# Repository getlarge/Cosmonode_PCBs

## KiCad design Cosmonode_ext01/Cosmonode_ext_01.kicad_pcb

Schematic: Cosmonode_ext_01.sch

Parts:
C1, C2, C3, C4: 100nF; C_0603_HandSoldering
J1: GS2
J3, J5: CONN_01X08; Socket_Strip_Straight_1x08_Pitch2.54mm
J4: Aloes_Logo; Aloes_mini
J6: OSHW_Logo; OSHW-Logo_5.7x6mm_SilkScreen
J8, J9: GS3
R1: 4.7k; R_0603_HandSoldering
U1: TSL2561T(6P-3.8X2.6MM); TMB6-1.55-3.8X2.6MM
U2: BMP180
U3: SI7020-A20-YM0R; SON100P300X300X80-7N

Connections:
+3V3: J5.2, J5.3, J9.1 (G1)
/A0: J3.6
/A1: J3.7
/A4: J5.6, U1.6 (SDA), U2.6 (SDA), U3.1 (SDA)
/A5: J5.7, U1.4 (SCL), U2.5 (SCL), U3.6 (SCL)
/A6: J3.8
/A7: J5.8
/BAT+: J5.1
/D3: J3.1, U1.5 (INT)
/D4: J3.2, J9.3 (G3)
/D5: J3.3
/D6: J3.4, J8.3 (G3)
/D7: J3.5
GND: J5.4, J5.5, J8.1 (G1)
unnamed: C1.1, C2.1, C3.1, C4.1, J1.1 (G1), J9.2 (G2), U1.1 (VDD), U2.2 (VDD), U2.3 (VDDIO), U3.5 (VDD)
unnamed: C1.2, C2.2, C3.2, C4.2, J8.2 (G2), R1.2, U1.3 (GND), U2.7 (GND), U3.2 (GND)
unnamed: J1.2 (G2), R1.1, U1.2 (ADDR)

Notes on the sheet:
D6 as GND
D4 as +3.3V

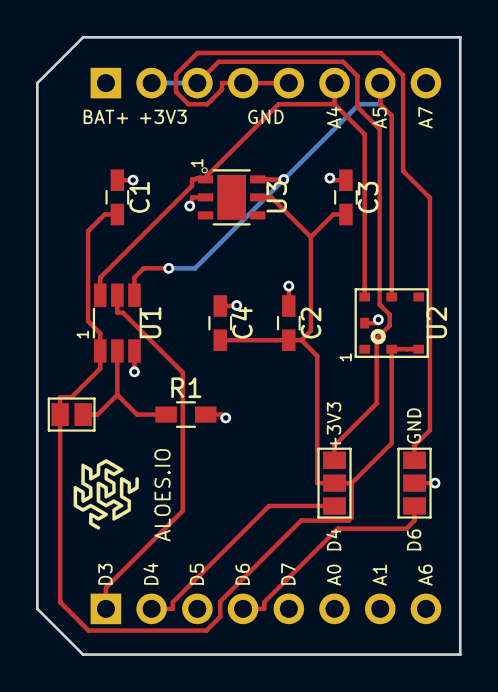
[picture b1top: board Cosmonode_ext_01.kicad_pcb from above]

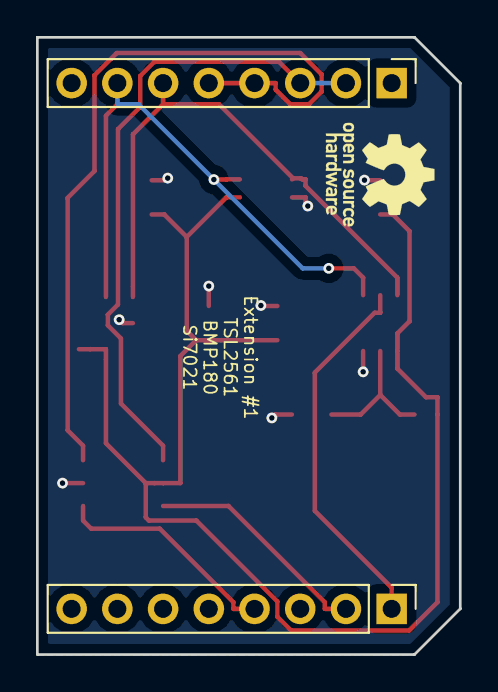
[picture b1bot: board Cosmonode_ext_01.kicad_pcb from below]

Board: 2 copper layers, 23.5 x 34.3 mm, 15 parts (3 on the bottom side), 10 nets.

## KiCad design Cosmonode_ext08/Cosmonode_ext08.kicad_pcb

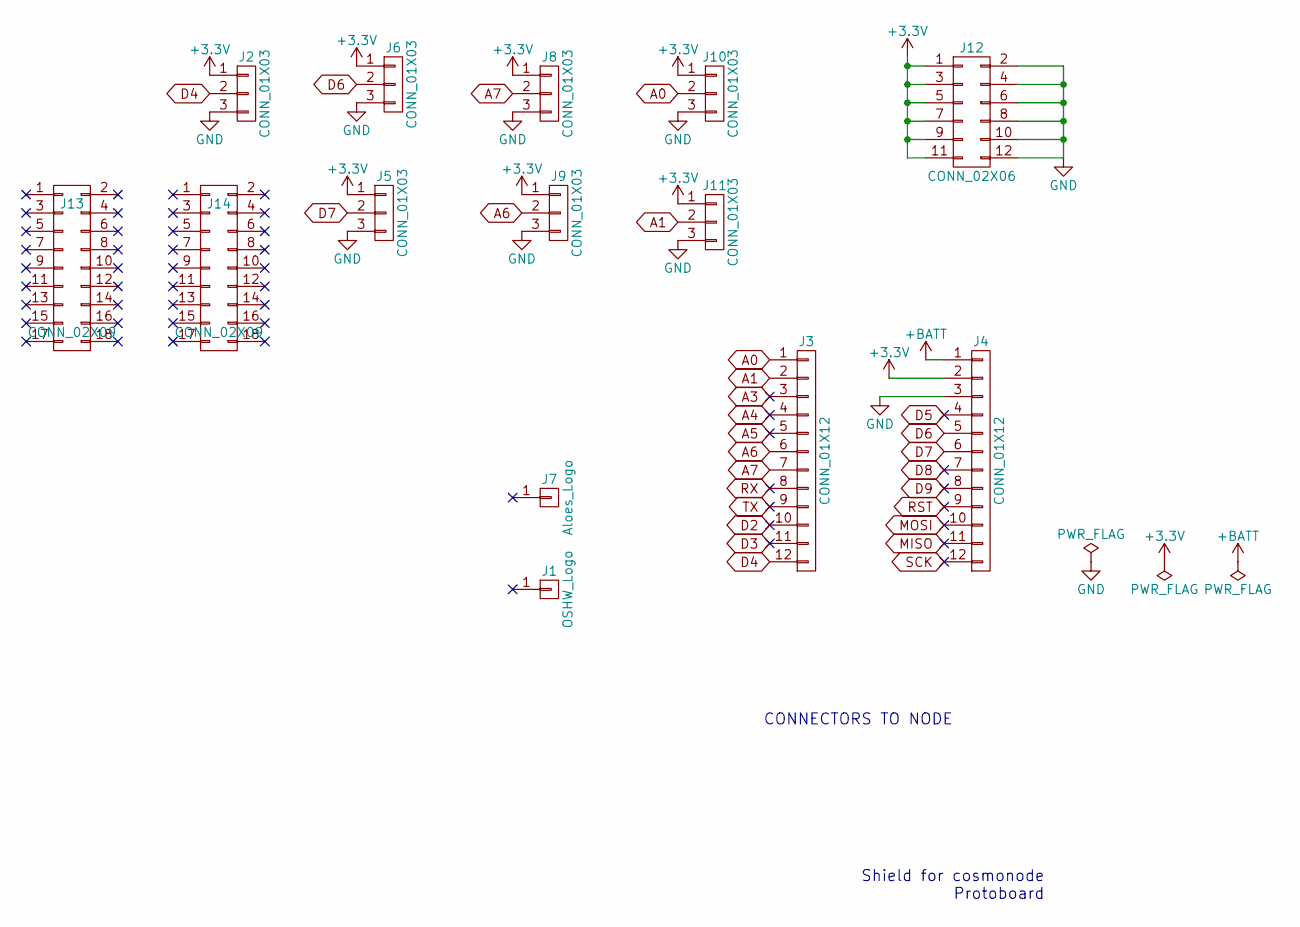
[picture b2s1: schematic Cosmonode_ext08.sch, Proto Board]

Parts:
J1: OSHW_Logo; OSHW-Logo_5.7x6mm_SilkScreen
J2, J5, J6, J8, J9, J10, J11: CONN_01X03; Pin_Header_Straight_1x03_Pitch2.54mm
J3, J4: CONN_01X12; Socket_Strip_Straight_1x12_Pitch2.54mm
J7: Aloes_Logo; Aloes_mini
J12: CONN_02X06; Pin_Header_Straight_2x06_Pitch2.54mm
J13, J14: CONN_02X09; Pin_Header_Straight_2x09_Pitch2.54mm

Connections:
+3V3: J2.1, J4.2, J5.1, J6.1, J8.1, J9.1, J10.1, J11.1, J12.1, J12.3, J12.5, J12.7, J12.9, J12.11
+BATT: J4.1
A0: J3.1, J10.2
A1: J3.2, J11.2
A3: J3.3
A4: J3.4
A5: J3.5
A6: J3.6, J9.2
A7: J3.7, J8.2
D2: J3.10
D3: J3.11
D4: J2.2, J3.12
D5: J4.4
D6: J4.5, J6.2
D7: J4.6, J5.2
D8: J4.7
D9: J4.8
GND: J2.3, J4.3, J5.3, J6.3, J8.3, J9.3, J10.3, J11.3, J12.2, J12.4, J12.6, J12.8, J12.10, J12.12
MISO: J4.11
MOSI: J4.10
RST: J4.9
RX: J3.8
SCK: J4.12
TX: J3.9

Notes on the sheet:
Shield for cosmonode Protoboard
CONNECTORS TO NODE

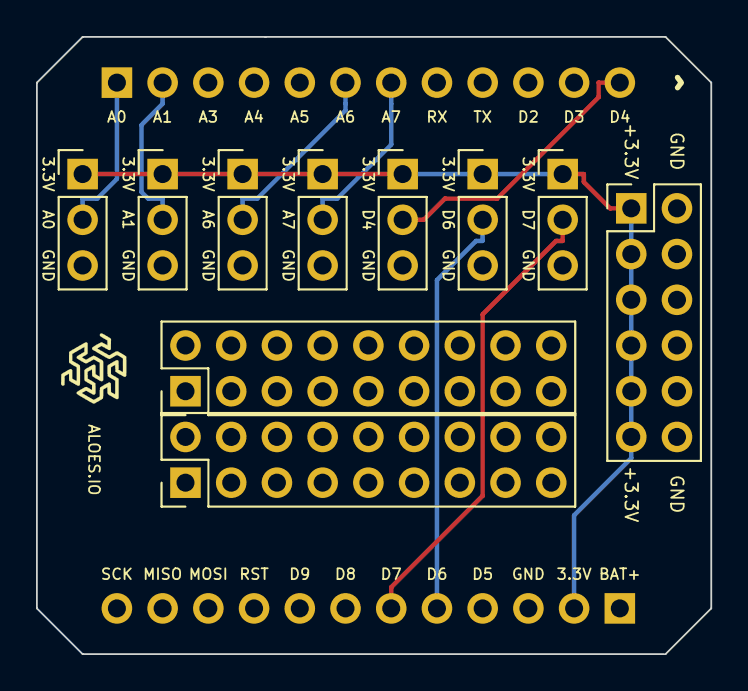
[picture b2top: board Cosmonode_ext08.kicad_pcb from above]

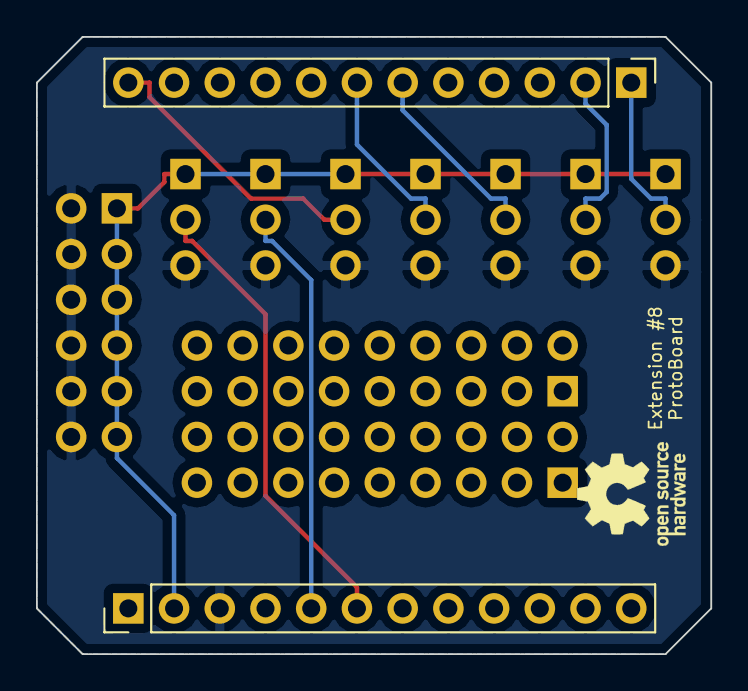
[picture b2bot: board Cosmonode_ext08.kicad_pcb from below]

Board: 2 copper layers, 37.5 x 34.3 mm, 14 parts (3 on the bottom side), 9 nets.

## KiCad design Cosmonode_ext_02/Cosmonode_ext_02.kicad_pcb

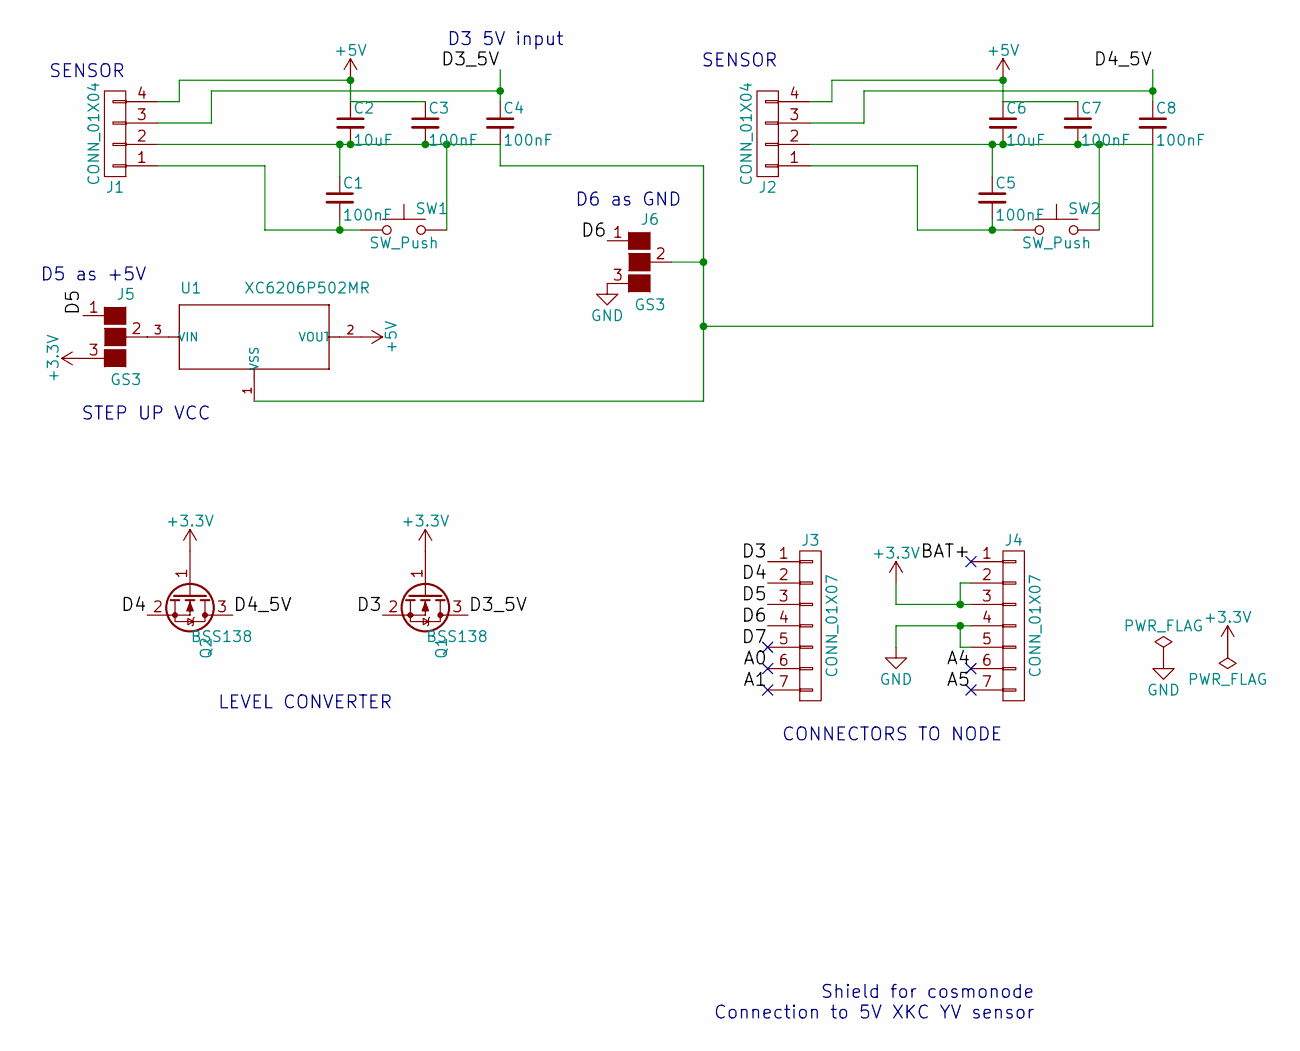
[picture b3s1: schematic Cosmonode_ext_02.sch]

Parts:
C1, C3, C4, C5, C7, C8: 100nF; C_0603_HandSoldering
C2, C6: 10uF; C_0603_HandSoldering
J1, J2: CONN_01X04; JST_XH_B04B-XH-A_04x2.50mm_Straight
J3, J4: CONN_01X07; Pin_Header_Straight_1x07_Pitch2.54mm
J5, J6: GS3
Q1, Q2: BSS138; SOT-23_Handsoldering
SW1, SW2: SW_Push; SW_SPST_B3U-1000P
U1: XC6206P502MR; SOT-23_Handsoldering

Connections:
+3V3: J4.2, J4.3, J5.3 (G3), Q1.1 (G), Q2.1 (G)
+5V: C2.1, C3.1, C6.1, C7.1, J1.4, J2.4, U1.2 (VOUT)
/A0: J3.6
/A1: J3.7
/A4: J4.6
/A5: J4.7
/BAT+: J4.1
/D3: J3.1, Q1.2 (S)
/D3_5V: C4.1, J1.3, Q1.3 (D)
/D4: J3.2, Q2.2 (S)
/D4_5V: C8.1, J2.3, Q2.3 (D)
/D5: J3.3, J5.1 (G1)
/D6: J3.4, J6.1 (G1)
/D7: J3.5
GND: J4.4, J4.5, J6.3 (G3)
unnamed: C1.1, C2.2, C3.2, C4.2, C5.1, C6.2, C7.2, C8.2, J1.2, J2.2, J6.2 (G2), SW1.2, SW2.2, U1.1 (VSS)
unnamed: C1.2, J1.1, SW1.1
unnamed: C5.2, J2.1, SW2.1
unnamed: J5.2 (G2), U1.3 (VIN)

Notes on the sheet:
D5 as +5V
D6 as GND
Shield for cosmonode Connection to 5V XKC YV sensor
D3 5V input
CONNECTORS TO NODE
LEVEL CONVERTER
STEP UP VCC
SENSOR

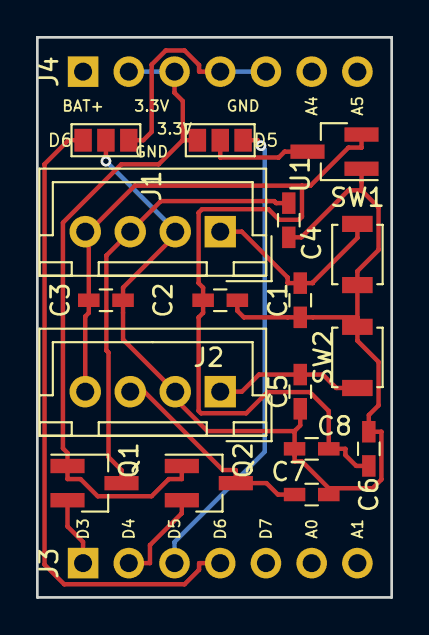
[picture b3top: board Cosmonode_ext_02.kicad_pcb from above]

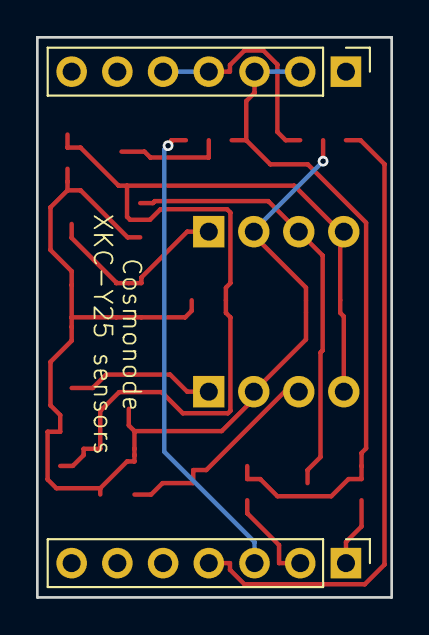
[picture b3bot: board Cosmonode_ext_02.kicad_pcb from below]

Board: 2 copper layers, 19.7 x 31.1 mm, 19 parts (2 on the bottom side), 13 nets.

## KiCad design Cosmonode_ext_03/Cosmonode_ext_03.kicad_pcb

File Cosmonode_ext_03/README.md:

# Cosmonode_ext_03

Extension 3 : includes 2 connectors for I2C 3.3V

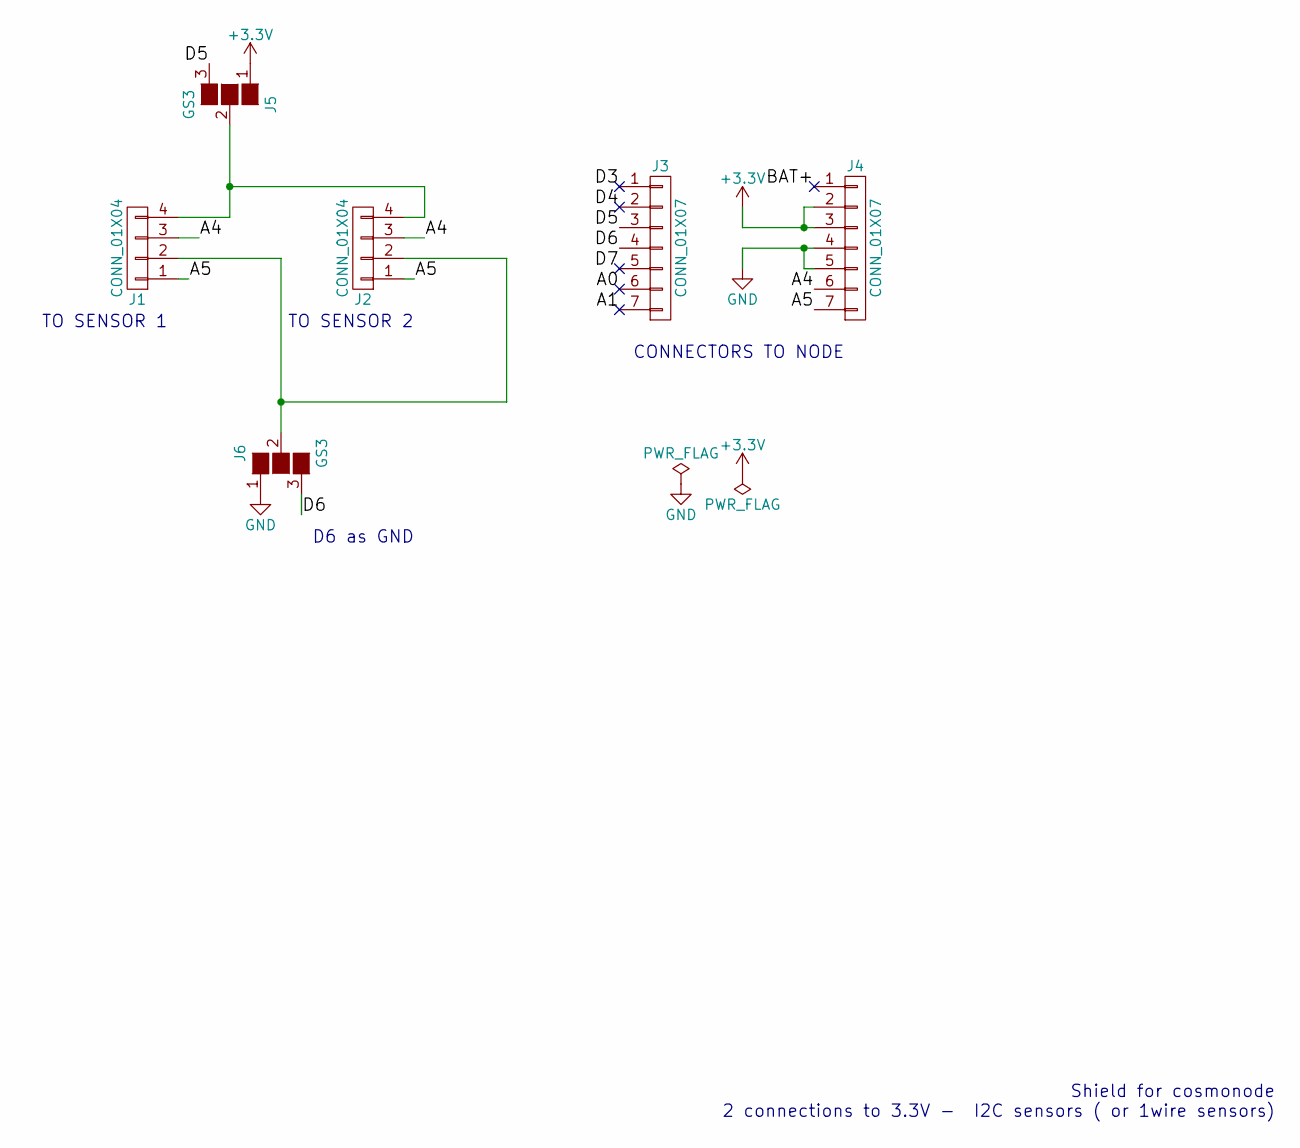
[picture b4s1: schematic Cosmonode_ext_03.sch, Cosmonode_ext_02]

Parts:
J1, J2: CONN_01X04; JST_XH_B04B-XH-A_04x2.50mm_Straight
J3, J4: CONN_01X07; Pin_Header_Straight_1x07_Pitch2.54mm
J5, J6: GS3

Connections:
+3V3: J4.2, J4.3, J5.1 (G1)
/A0: J3.6
/A1: J3.7
/A4: J1.3, J2.3, J4.6
/A5: J1.1, J2.1, J4.7
/BAT+: J4.1
/D3: J3.1
/D4: J3.2
/D5: J3.3, J5.3 (G3)
/D6: J3.4, J6.3 (G3)
/D7: J3.5
GND: J4.4, J4.5, J6.1 (G1)
unnamed: J1.2, J2.2, J6.2 (G2)
unnamed: J1.4, J2.4, J5.2 (G2)

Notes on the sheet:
D6 as GND
Shield for cosmonode 2 connections to 3.3V - I2C sensors ( or 1wire sensors)
CONNECTORS TO NODE
TO SENSOR 1
TO SENSOR 2

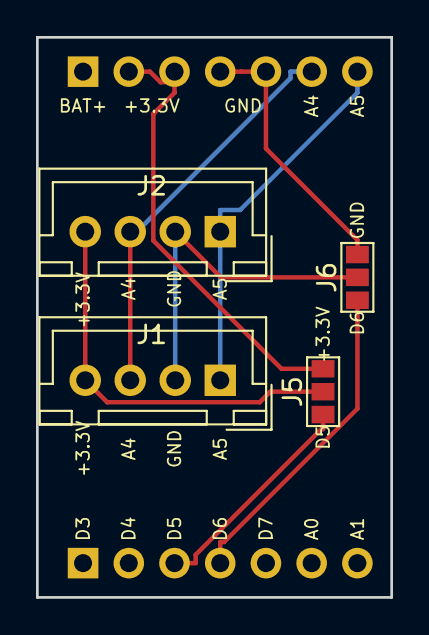
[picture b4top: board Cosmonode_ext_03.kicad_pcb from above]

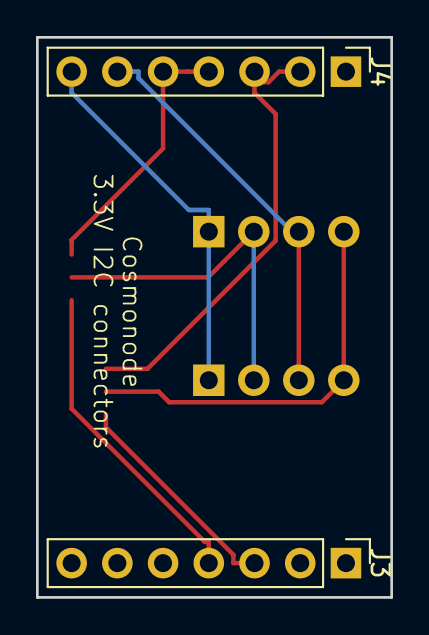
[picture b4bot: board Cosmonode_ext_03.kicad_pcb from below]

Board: 2 copper layers, 19.7 x 31.1 mm, 6 parts (2 on the bottom side), 8 nets.

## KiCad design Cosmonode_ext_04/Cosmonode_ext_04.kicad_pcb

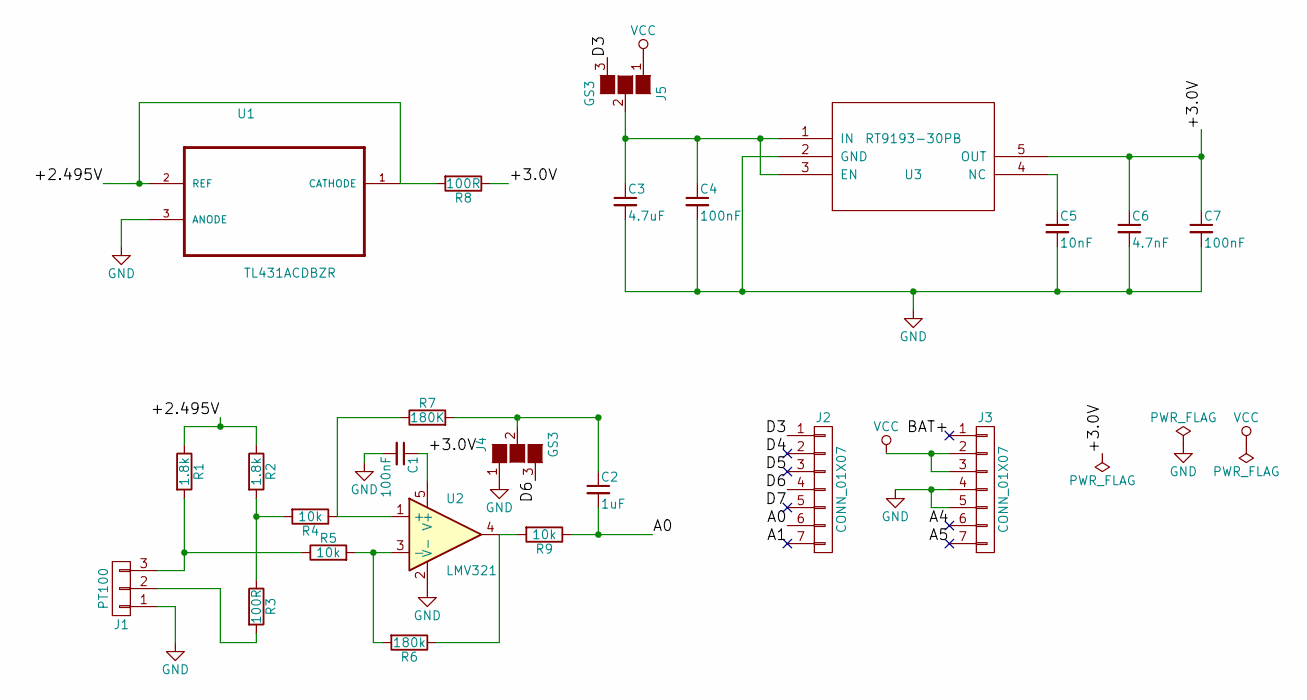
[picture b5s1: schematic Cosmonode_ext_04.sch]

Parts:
C1, C4, C7: 100nF; C_0603_HandSoldering
C2: 1uF; C_0603_HandSoldering
C3: 4.7uF; C_0603_HandSoldering
C5: 10nF; C_0603_HandSoldering
C6: 4.7nF; C_0603_HandSoldering
J1: PT100; JST_PH_B3B-PH-K_03x2.00mm_Straight
J2, J3: CONN_01X07; Pin_Header_Straight_1x07_Pitch2.54mm
J4, J5: GS3
R1, R2: 1.8k; R_0603_HandSoldering
R3, R8: 100R; R_0603_HandSoldering
R4, R5, R9: 10k; R_0603_HandSoldering
R6: 180k; R_0603_HandSoldering
R7: 180K; R_0603_HandSoldering
U1: TL431ACDBZR; SOT-23_Handsoldering
U2: LMV321; SOT-23-5_HandSoldering
U3: RT9193-30PB; SOT-23-5_HandSoldering

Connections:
/+2.495V: R1.1, R2.1, R8.2, U1.1 (CATHODE), U1.2 (REF)
/+3.0V: C1.1, C6.1, C7.1, R8.1, U2.5 (V+), U3.5 (OUT)
/A0: C2.2, J2.6, R9.1
/A1: J2.7
/A4: J3.6
/A5: J3.7
/BAT+: J3.1
/D3: J2.1, J5.3 (G3)
/D4: J2.2
/D5: J2.3
/D6: J2.4, J4.3 (G3)
/D7: J2.5
GND: C1.2, C3.2, C4.2, C5.2, C6.2, C7.2, J1.1, J3.4, J3.5, J4.1 (G1), U1.3 (ANODE), U2.2 (V-), U3.2 (GND)
unnamed: C2.1, J4.2 (G2), R7.2
unnamed: C3.1, C4.1, J5.2 (G2), U3.1 (IN), U3.3 (EN)
unnamed: C5.1, U3.4 (NC)
unnamed: J1.2, R3.2
unnamed: J1.3, R1.2, R5.1
unnamed: R2.2, R3.1, R4.2
unnamed: R4.1, R7.1, U2.1 (+)
unnamed: R5.2, R6.2, U2.3 (-)
unnamed: R6.1, R9.2, U2.4
VCC: J3.2, J3.3, J5.1 (G1)

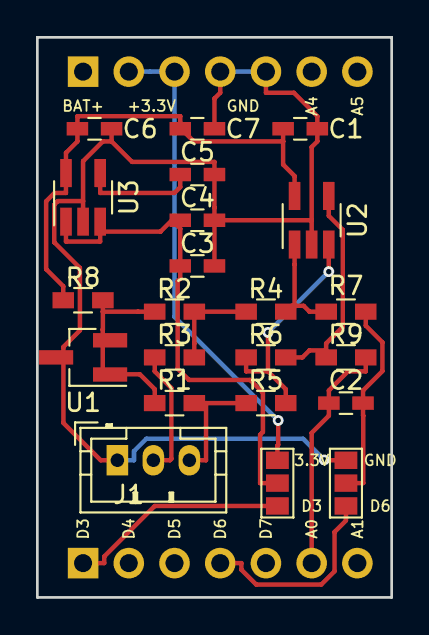
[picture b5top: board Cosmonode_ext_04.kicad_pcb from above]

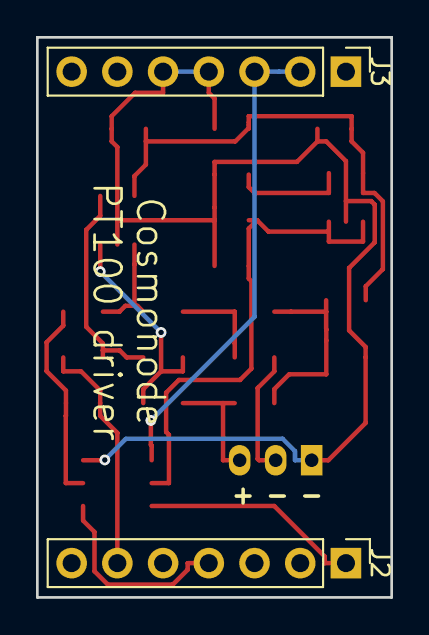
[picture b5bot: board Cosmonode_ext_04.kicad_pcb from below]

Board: 2 copper layers, 19.7 x 31.1 mm, 24 parts (2 on the bottom side), 16 nets.
